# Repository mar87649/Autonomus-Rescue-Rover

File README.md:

# Autonomous-Room-Mapping-Robot

# Description: 
Room mapping robot that can detect and avoid obstacles. 
Room is displayed in 2D via GUI.

# Status: 
Development has stopped

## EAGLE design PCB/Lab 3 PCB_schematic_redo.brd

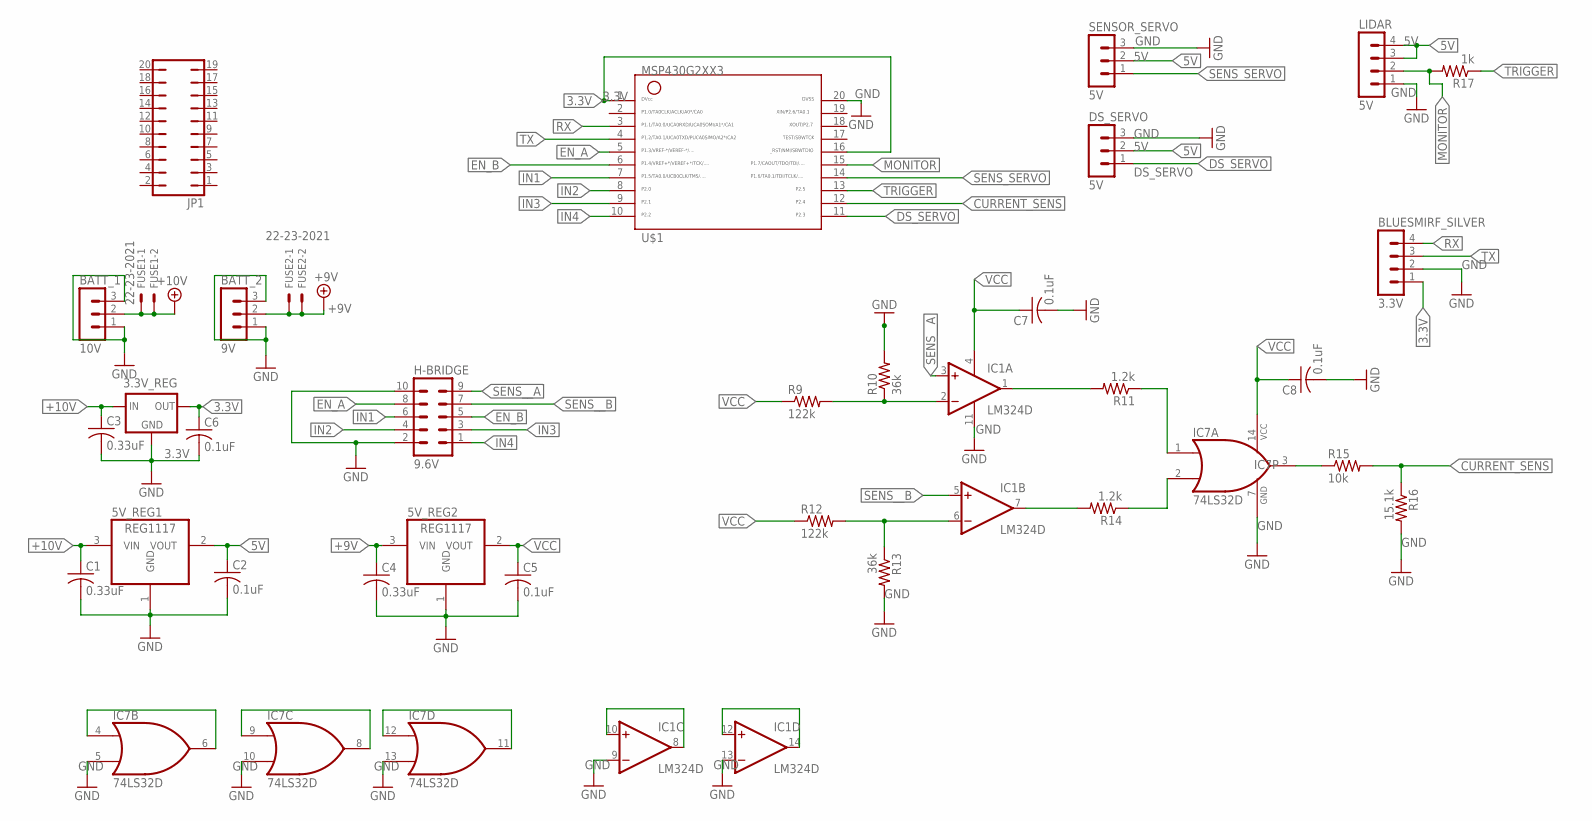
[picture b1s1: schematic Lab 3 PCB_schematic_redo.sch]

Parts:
3.3V_REG: 3.3V; 78LXX
5V_REG1, 5V_REG2: REG1117; SOT223
BATT_1: 10V; MA03-1
BATT_2: 9V; MA03-1
BLUESMIRF_SILVER: 3.3V; MA04-1
C1, C3, C4: 0.33uF; C025-024X044
C2, C5, C6, C7, C8: 0.1uF; C025-024X044
DS_SERVO: 5V; MA03-1
FUSE1, FUSE2: 22-23-2021
H-BRIDGE: 9.6V; MA05-2
IC1: LM324D; SO14
IC7: 74LS32D; SO14
JP1: JP10Q
LIDAR: 5V; MA04-1
R9, R12: 122k; R0805
R10, R13: 36k; R0805
R11, R14: 1.2k; R0805
R15: 10k; R0805
R16: 15.1k; R0805
R17: 1k; R0805
SENSOR_SERVO: 5V; MA03-1
U$1: G2XX3---N20; N20

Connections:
3.3V: 3.3V_REG.OUT, BLUESMIRF_SILVER.1, C6.1, U$1.1, U$1.16
5V: 5V_REG1.2 (VOUT), C2.1, DS_SERVO.2, LIDAR.3, LIDAR.4, SENSOR_SERVO.2
+9V: 5V_REG2.3 (VIN), BATT_2.2, C4.1, FUSE2.1, FUSE2.2
+10V: 3.3V_REG.IN, 5V_REG1.3 (VIN), BATT_1.2, C1.1, C3.1, FUSE1.1, FUSE1.2
CURRENT_SENS: R15.2, R16.1, U$1.12
DS_SERVO: DS_SERVO.1, U$1.11
EN_A: H-BRIDGE.8, U$1.5
EN_B: H-BRIDGE.5, U$1.6
GND: 3.3V_REG.GND, 5V_REG1.1 (GND), 5V_REG2.1 (GND), BATT_1.1, BATT_1.3, BATT_2.1, BATT_2.3, BLUESMIRF_SILVER.2, C1.2, C2.2, C3.2, C4.2, C5.2, C6.2, C7.2, C8.2, DS_SERVO.3, H-BRIDGE.2, H-BRIDGE.10, IC1.9 (-IN), IC1.11 (V-), IC1.13 (-IN), IC7.5 (I1), IC7.7 (GND), IC7.10 (I1), IC7.13 (I1), LIDAR.1, R10.2, R13.2, R16.2, SENSOR_SERVO.3, U$1.20
IN1: H-BRIDGE.6, U$1.7
IN2: H-BRIDGE.4, U$1.8
IN3: H-BRIDGE.3, U$1.9
IN4: H-BRIDGE.1, U$1.10
MONITOR: LIDAR.2, R17.2, U$1.15
unnamed: IC7.4 (I0), IC7.6 (O)
unnamed: IC1.6 (-IN), R12.2, R13.1
unnamed: IC1.2 (-IN), R9.2, R10.1
unnamed: IC7.1 (I0), R11.1
unnamed: IC1.8 (OUT), IC1.10 (+IN)
unnamed: IC1.1 (OUT), R11.2
unnamed: IC1.7 (OUT), R14.2
unnamed: IC7.2 (I1), R14.1
unnamed: IC7.3 (O), R15.1
unnamed: IC7.8 (O), IC7.9 (I0)
unnamed: IC7.11 (O), IC7.12 (I0)
unnamed: IC1.12 (+IN), IC1.14 (OUT)
RX: BLUESMIRF_SILVER.4, U$1.3
SENS_SERVO: SENSOR_SERVO.1, U$1.14
SENS__A: H-BRIDGE.9, IC1.3 (+IN)
SENS__B: H-BRIDGE.7, IC1.5 (+IN)
TRIGGER: R17.1, U$1.13
TX: BLUESMIRF_SILVER.3, U$1.4
VCC: 5V_REG2.2 (VOUT), C5.1, C7.1, C8.1, IC1.4 (V+), IC7.14 (VCC), R9.1, R12.1

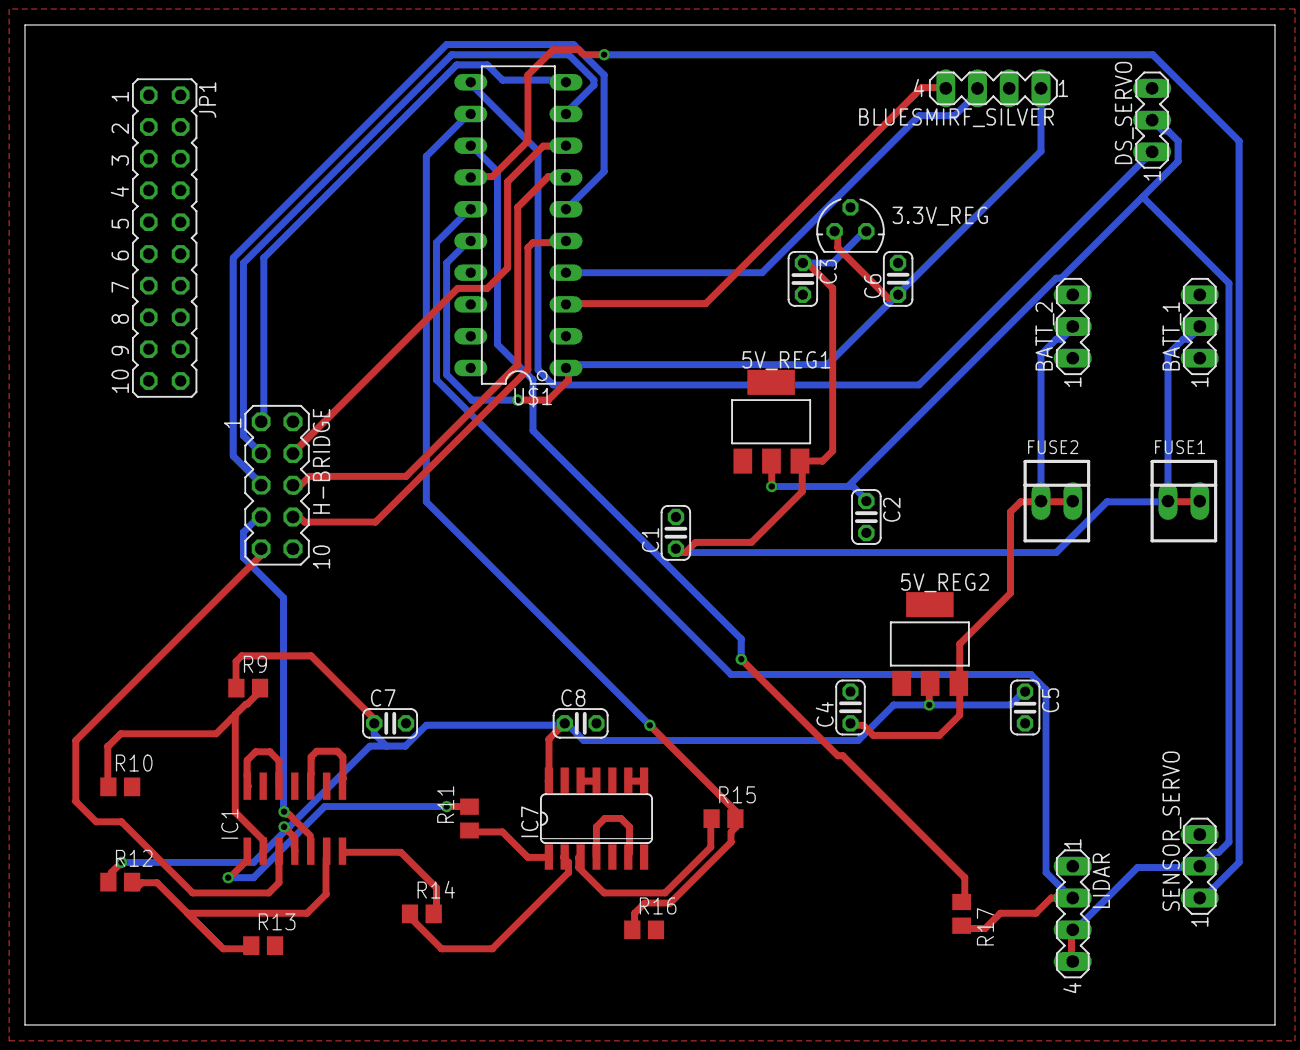
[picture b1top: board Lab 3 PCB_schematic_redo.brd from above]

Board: 2 copper layers, 100.0 x 80.0 mm, 33 parts (0 on the bottom side), 33 nets.
